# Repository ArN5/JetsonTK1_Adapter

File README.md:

# JetsonTK1_Adapter
This small circuit board will allow you to access the I/O pins from the Jetson TK1. Convert from 2MM pitch into standard 2.54MM headers.
You will have access to the 12v, 5v, 3.3v 1.8v rails as well as two I2C ports.
http://www.jarzebski.pl/files/jetsontk1/jetson-expsansion-800.jpg
We used this module to interface various I2C sensors to our Jetson 
TK1 board.

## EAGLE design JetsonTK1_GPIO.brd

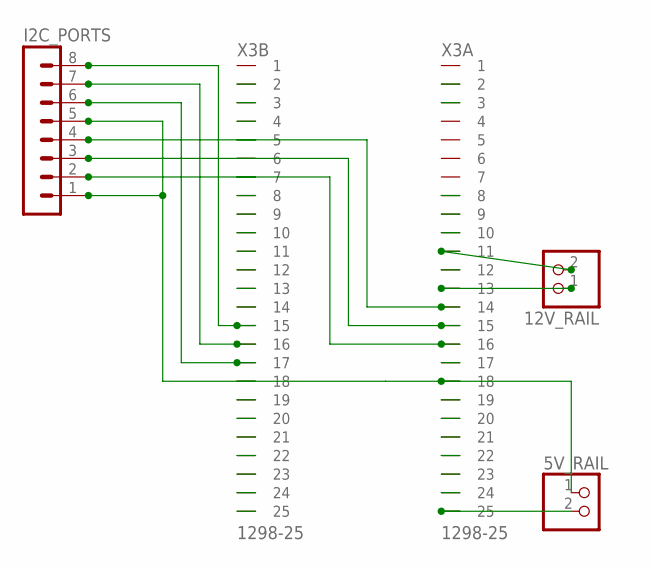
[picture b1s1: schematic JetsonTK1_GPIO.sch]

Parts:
5V_RAIL, 12V_RAIL: PINHD-1X2; 1X02
I2C_PORTS: MA08-1
X3: 1298-25

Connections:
1.8V: I2C_PORTS.2, X3.A16 (16)
3.3V: I2C_PORTS.8, X3.B15 (15)
12V: 12V_RAIL.1, X3.A13 (13)
GND: 5V_RAIL.1, I2C_PORTS.1, I2C_PORTS.5, X3.A18 (18)
GND_12VRAIL: 12V_RAIL.2, X3.A11 (11)
unnamed: 5V_RAIL.2, X3.A25 (25)
SCL_1.8V_0: I2C_PORTS.3, X3.A15 (15)
SCL_3.3V_1: I2C_PORTS.6, X3.B17 (17)
SDA_1.8V_0: I2C_PORTS.4, X3.A14 (14)
SDA_3.3V_1: I2C_PORTS.7, X3.B16 (16)

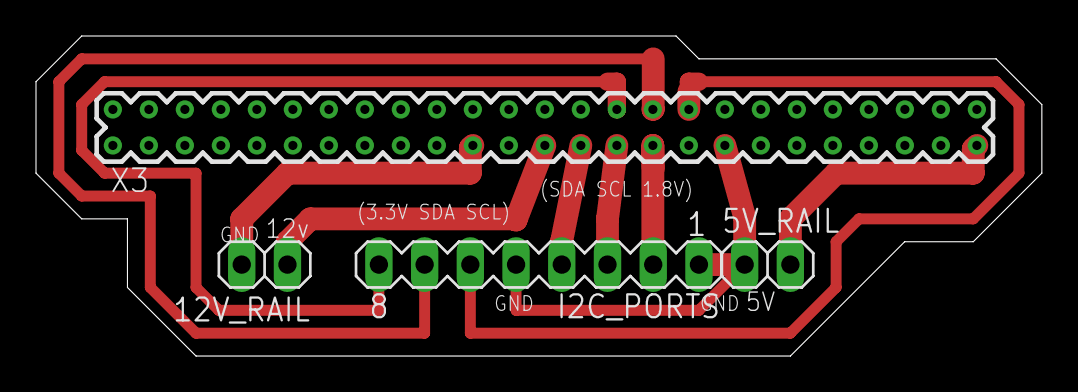
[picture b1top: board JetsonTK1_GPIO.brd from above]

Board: 2 copper layers, 55.9 x 17.8 mm, 4 parts (0 on the bottom side), 10 nets.

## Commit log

2016-12-13 V2 is double sided
    You can order these PCB through Dirty PCB
